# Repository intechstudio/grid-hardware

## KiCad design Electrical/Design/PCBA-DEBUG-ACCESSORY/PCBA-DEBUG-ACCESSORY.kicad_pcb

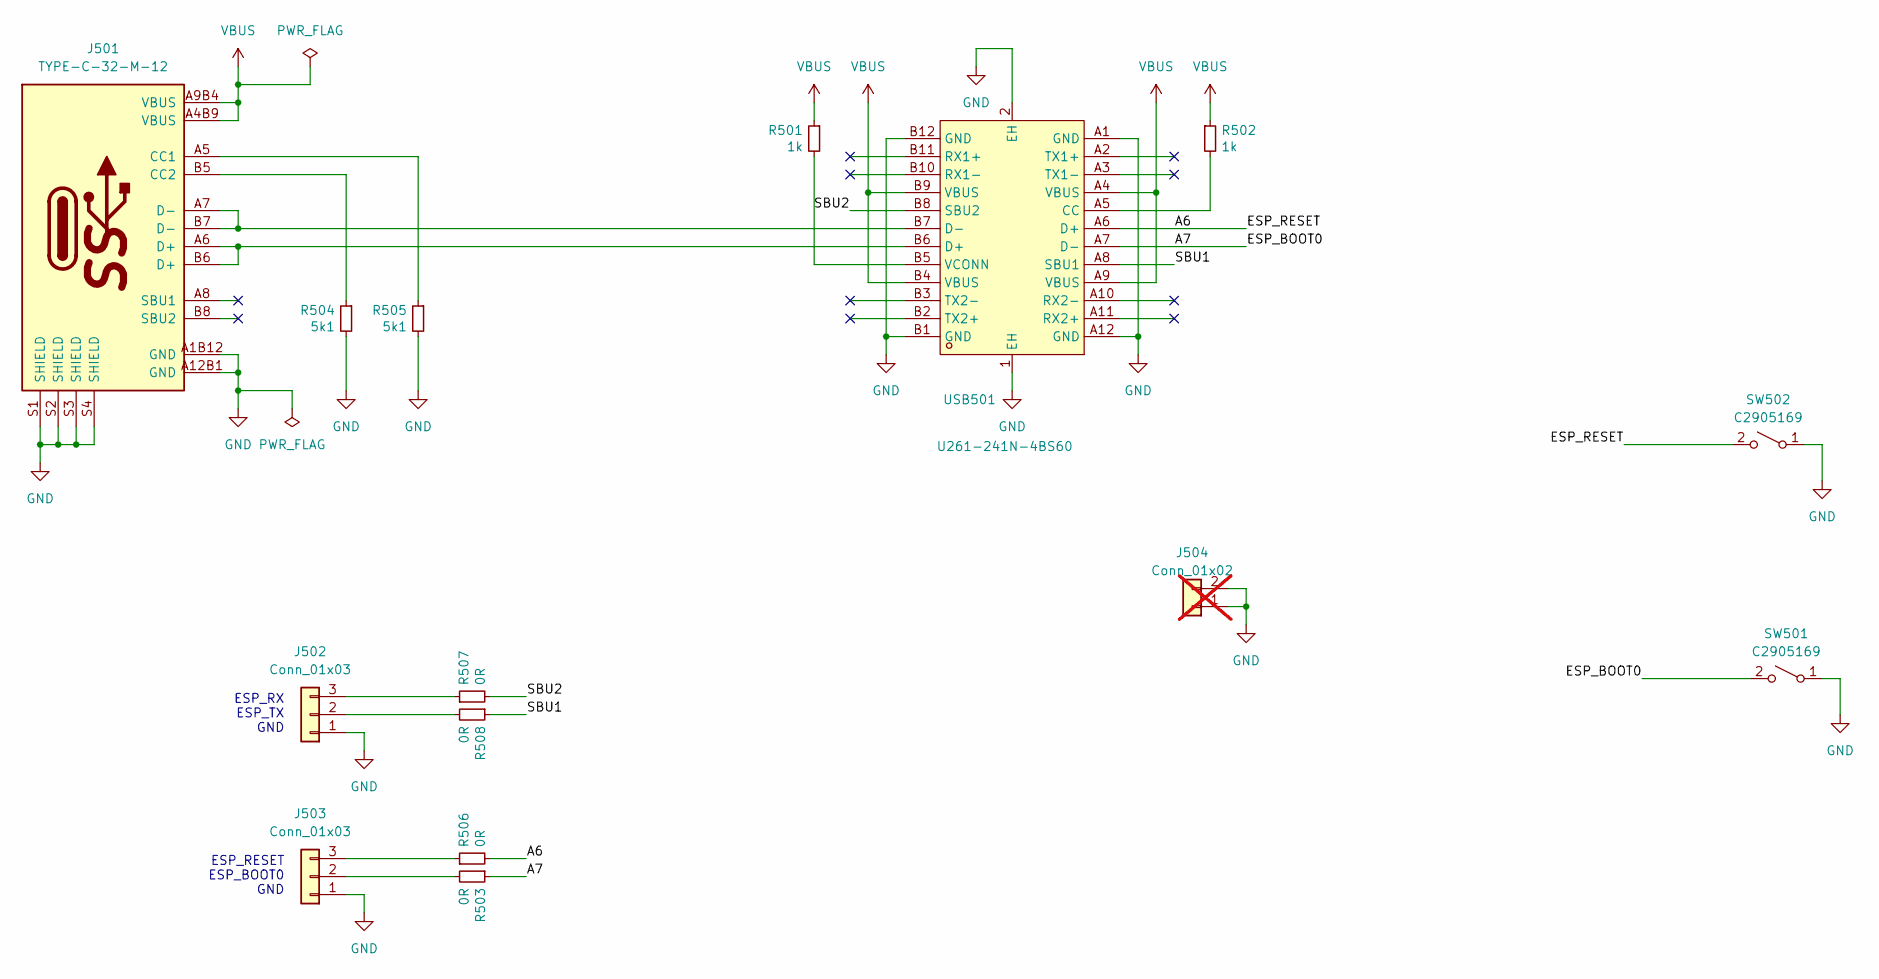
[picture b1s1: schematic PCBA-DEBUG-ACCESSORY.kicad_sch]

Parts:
J501: TYPE-C-32-M-12; USB_C_Korean_Hroparts_TYPE-C-31-M-12
J502, J503: Conn_01x03; PinHeader_1x03_P2.54mm_Vertical
J504: Conn_01x02; OscilloscopeGround; not fitted
R501, R502: 1k; RES_0402
R503, R506, R507, R508: 0R; RES_0402
R504, R505: 5k1; RES_0402
SW501, SW502: C2905169; SW_SPST_CK_RS282G05A3
USB501: U261-241N-4BS60; USB-TYPE-C-SMD_U261-241N-4BS60; LCSC Part C319150

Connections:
/A6: R506.2, SW502.2 (B), USB501.A6 (D+)
/A7: R503.1, SW501.2 (B), USB501.A7 (D-)
/SBU1: R508.1, USB501.A8 (SBU1)
/SBU2: R507.2, USB501.B8 (SBU2)
GND: J501.A1B12 (GND), J501.A12B1 (GND), J501.S1 (SHIELD), J501.S2 (SHIELD), J501.S3 (SHIELD), J501.S4 (SHIELD), J502.1, J503.1, J504.1, J504.2, R504.2, R505.2, SW501.1 (A), SW502.1 (A), USB501.1 (EH), USB501.2 (EH), USB501.A1 (GND), USB501.A12 (GND), USB501.B1 (GND), USB501.B12 (GND)
unnamed: J501.A5 (CC1), R505.1
unnamed: J501.B5 (CC2), R504.1
unnamed: J501.A6 (D+), J501.B6 (D+), USB501.B6 (D+)
unnamed: J501.A7 (D-), J501.B7 (D-), USB501.B7 (D-)
unnamed: J502.2, R508.2
unnamed: J502.3, R507.1
unnamed: J503.2, R503.2
unnamed: J503.3, R506.1
unnamed: R502.2, USB501.A5 (CC)
unnamed: R501.2, USB501.B5 (VCONN)
VBUS: J501.A4B9 (VBUS), J501.A9B4 (VBUS), R501.1, R502.1, USB501.A4 (VBUS), USB501.A9 (VBUS), USB501.B4 (VBUS), USB501.B9 (VBUS)

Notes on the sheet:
ESP_RESET ESP_BOOT0 GND
ESP_RX ESP_TX GND

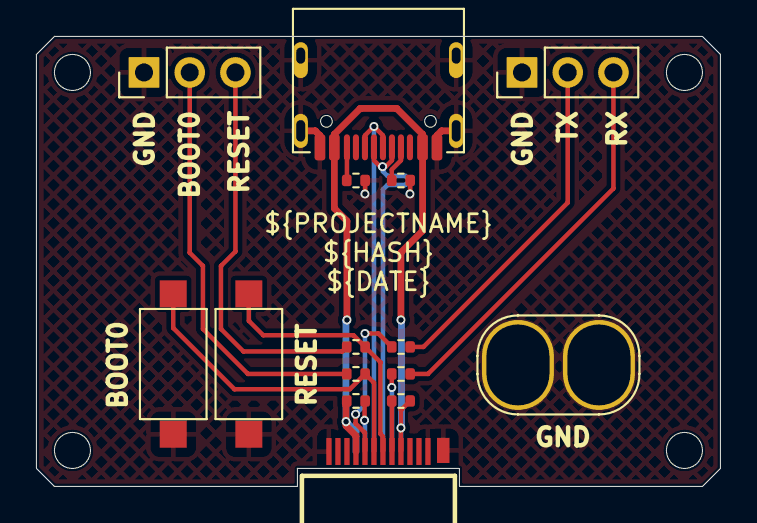
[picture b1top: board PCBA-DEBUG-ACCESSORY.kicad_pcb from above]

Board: 2 copper layers, 38.0 x 25.0 mm, 16 parts (1 on the bottom side), 16 nets.

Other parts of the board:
H534: Outline; OSHWA

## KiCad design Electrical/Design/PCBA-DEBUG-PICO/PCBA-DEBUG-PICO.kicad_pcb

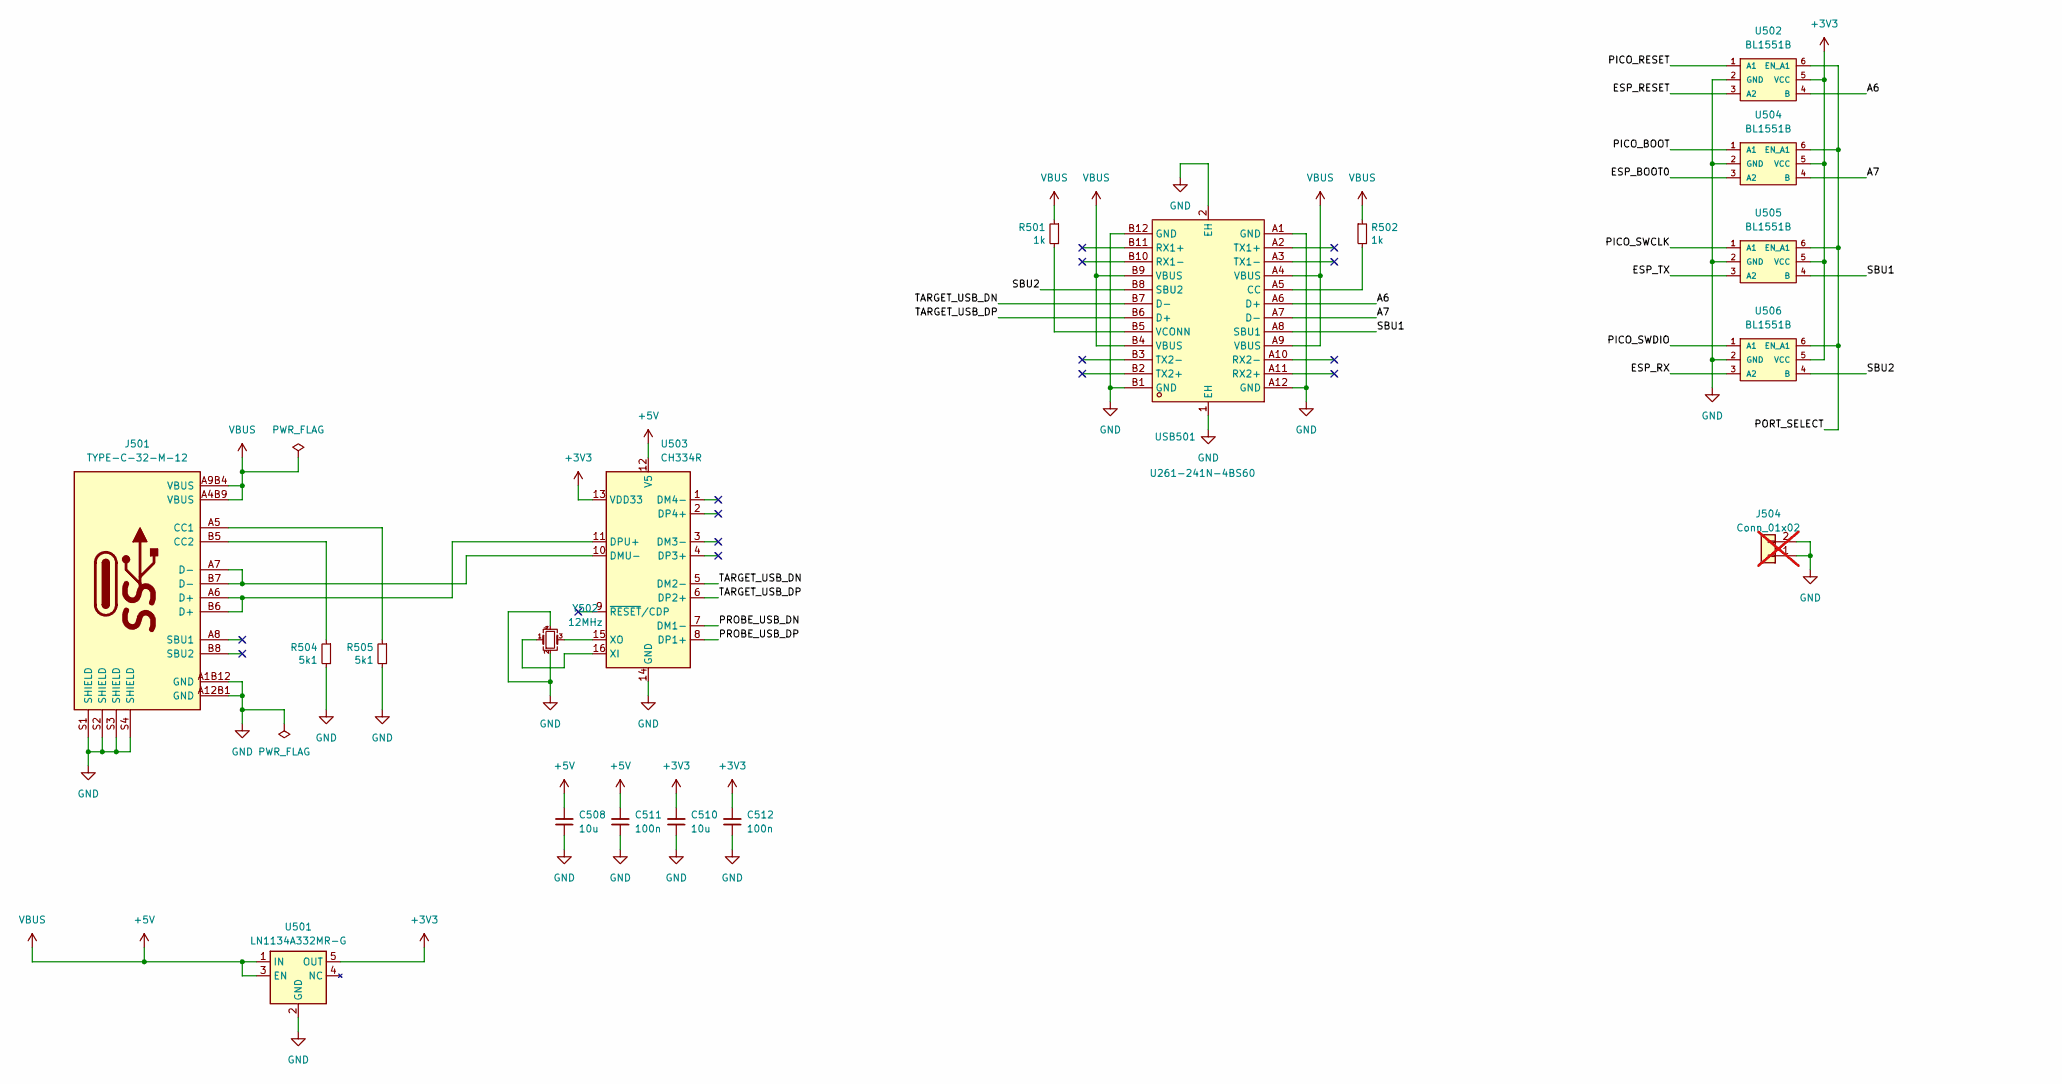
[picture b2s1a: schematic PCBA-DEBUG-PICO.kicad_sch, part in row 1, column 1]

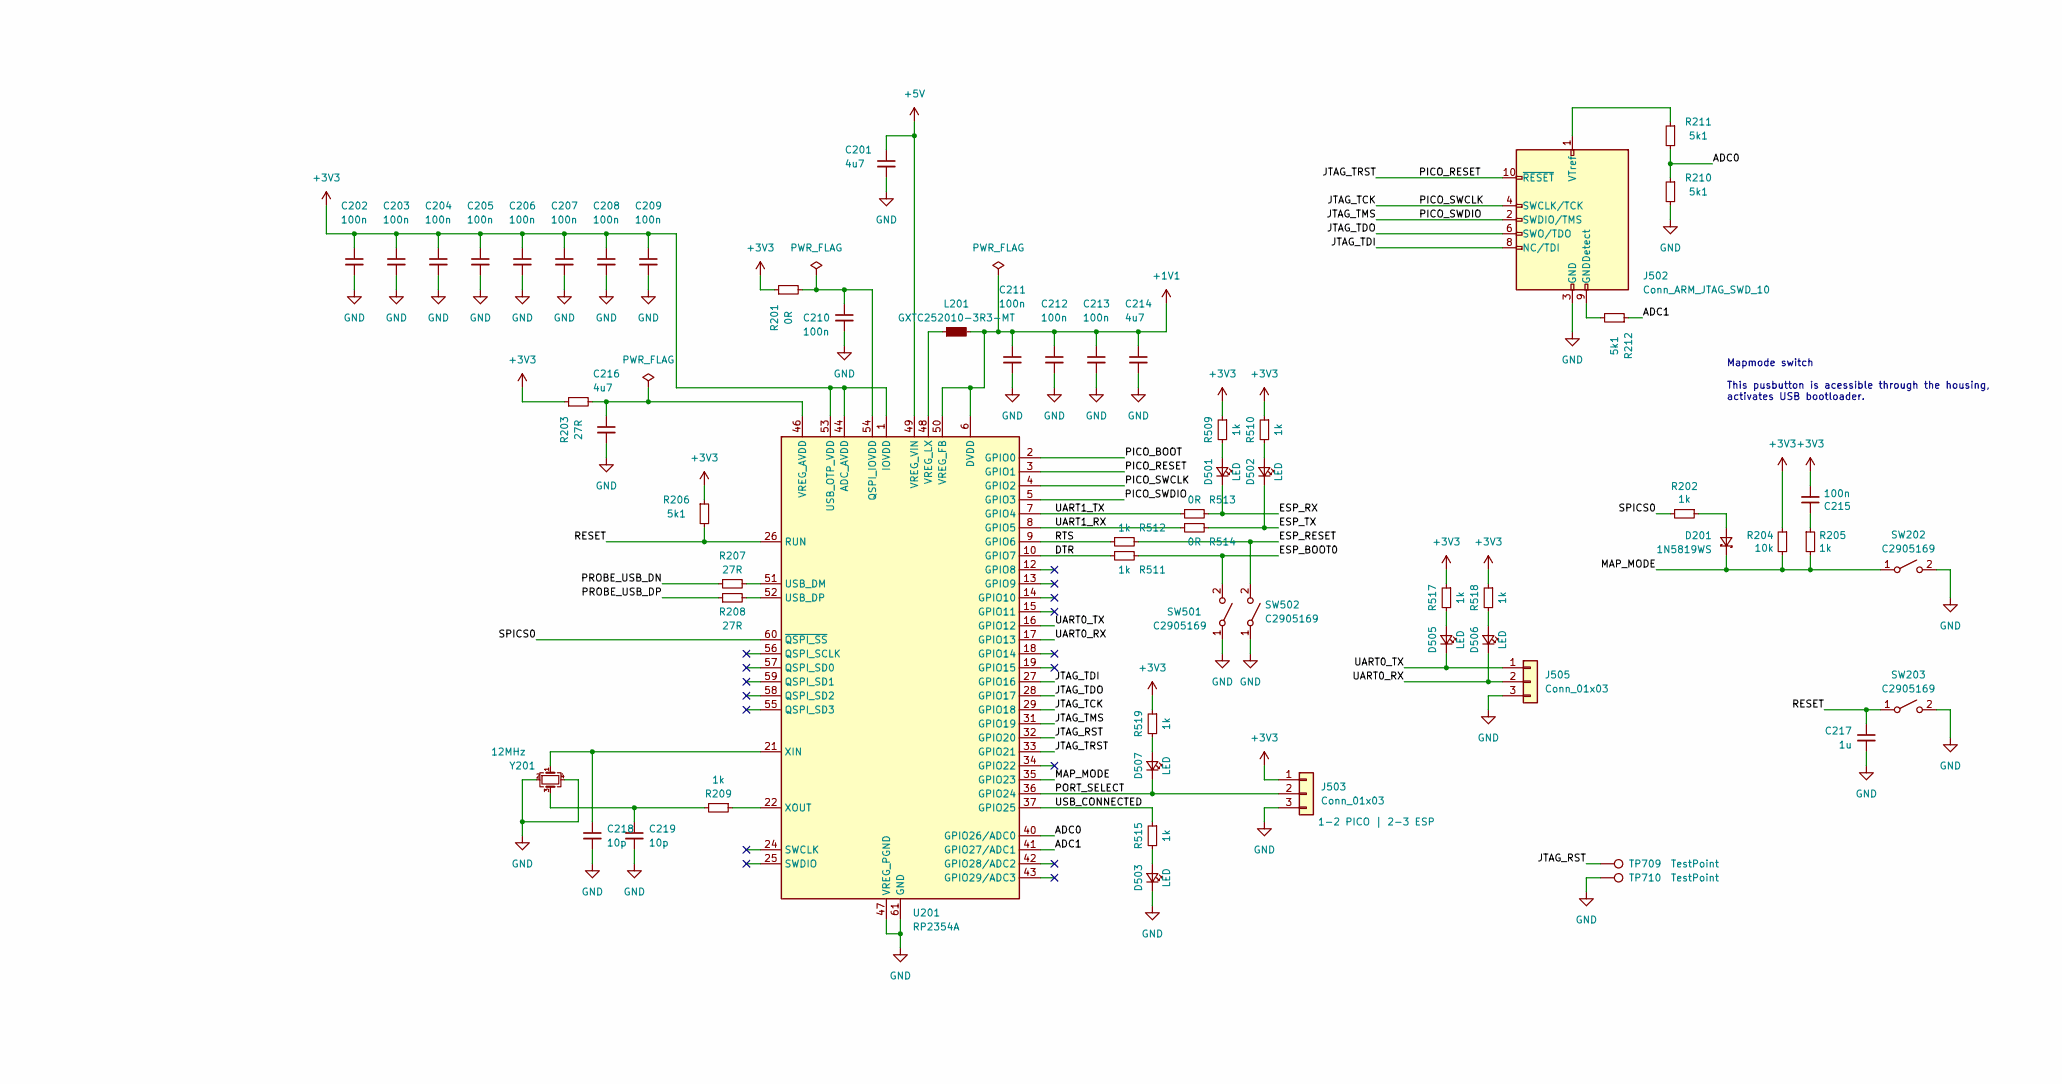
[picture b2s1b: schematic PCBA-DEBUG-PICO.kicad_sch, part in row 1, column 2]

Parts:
C201, C214, C216: 4u7; CAP_0402
C202, C203, C204, C205, C206, C207, C208, C209, C210, C211, C212, C213, C215, C511, C512: 100n; CAP_0402
C217: 1u; CAP_0402
C218, C219: 10p; CAP_0402
C508, C510: 10u; CAP_0402
D201: 1N5819WS; D_SOD-323
D501, D502, D503, D505, D506, D507: LED; LED_0402_1005Metric
J501: TYPE-C-32-M-12; USB_C_Korean_Hroparts_TYPE-C-31-M-12
J502: Conn_ARM_JTAG_SWD_10; IDC-SMD_10P-P1.27-3220-10-0300-00
J503, J505: Conn_01x03; PinHeader_1x03_P2.54mm_Vertical_SMD_Pin1Left
J504: Conn_01x02; OscilloscopeGround; not fitted
L201: GXTC252010-3R3-MT; L_1008_2520Metric
R201, R513, R514: 0R; RES_0402
R202, R205, R209, R501, R502, R509, R510, R511, R512, R515, R517, R518, R519: 1k; RES_0402
R203, R207, R208: 27R; RES_0402
R204: 10k; RES_0402
R206, R210, R211, R212, R504, R505: 5k1; RES_0402
SW202, SW203, SW501, SW502: C2905169; SW_SPST_CK_RS282G05A3
TP709: TestPoint; TestPoint_Pad_D1.0mm
TP710: TestPoint; TestPoint_Pad_1.0x1.0mm
U201: RP2354A; QFN-60-1EP_7x7mm_P0.4mm_EP3.4x3.4mm
U501: LN1134A332MR-G; SOT-23-5
U502, U504, U505, U506: BL1551B; SOT-363_SC-70-6
U503: CH334R; QSOP-16_3.9x4.9mm_P0.635mm
USB501: U261-241N-4BS60; USB-TYPE-C-SMD_U261-241N-4BS60; LCSC Part C319150
Y201, Y502: 12MHz; Crystal_SMD_Abracon_ABM8G-4Pin_3.2x2.5mm

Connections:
+1V1: C211.1, C212.1, C213.1, C214.1, L201.2, U201.6 (DVDD), U201.23 (DVDD), U201.39 (DVDD), U201.50 (VREG_FB)
+3V3: C202.1, C203.1, C204.1, C205.1, C206.1, C207.1, C208.1, C209.1, C215.2, C510.2, C512.2, J503.1, R201.1, R203.1, R204.1, R206.1, R509.1, R510.1, R517.1, R518.1, R519.1, U201.1 (IOVDD), U201.11 (IOVDD), U201.20 (IOVDD), U201.30 (IOVDD), U201.38 (IOVDD), U201.44 (ADC_AVDD), U201.45 (IOVDD), U201.53 (USB_OTP_VDD), U501.5 (OUT), U502.5 (VCC), U503.13 (VDD33), U504.5 (VCC), U505.5 (VCC), U506.5 (VCC)
+5V: C201.1, C508.2, C511.2, J501.A4B9 (VBUS), J501.A9B4 (VBUS), R501.1, R502.1, U201.49 (VREG_VIN), U501.1 (IN), U501.3 (EN), U503.12 (V5), USB501.A4 (VBUS), USB501.A9 (VBUS), USB501.B4 (VBUS), USB501.B9 (VBUS)
/A6: U502.4 (B), USB501.A6 (D+)
/A7: U504.4 (B), USB501.A7 (D-)
/ADC0: R210.1, R211.2, U201.40 (GPIO26/ADC0)
/ADC1: R212.1, U201.41 (GPIO27/ADC1)
/DTR: R511.1, U201.10 (GPIO7)
/ESP_BOOT0: R511.2, SW501.2 (B), U504.3 (A2)
/ESP_RESET: R512.2, SW502.2 (B), U502.3 (A2)
/ESP_RX: D501.1 (K), R513.2, U506.3 (A2)
/ESP_TX: D502.1 (K), R514.2, U505.3 (A2)
/JTAG_RST: TP709.1 (1_1), U201.32 (GPIO20)
/JTAG_TCK: J502.4 (SWCLK/TCK), U201.4 (GPIO2), U201.29 (GPIO18), U505.1 (A1)
/JTAG_TDI: J502.8 (NC/TDI), U201.27 (GPIO16)
/JTAG_TDO: J502.6 (SWO/TDO), U201.28 (GPIO17)
/JTAG_TMS: J502.2 (SWDIO/TMS), U201.5 (GPIO3), U201.31 (GPIO19), U506.1 (A1)
/JTAG_TRST: J502.10 (~RESET), U201.3 (GPIO1), U201.33 (GPIO21), U502.1 (A1)
/MAP_MODE: D201.1 (K), R204.2, R205.2, SW202.1 (A), U201.35 (GPIO23)
/PICO_BOOT: U201.2 (GPIO0), U504.1 (A1)
/PORT_SELECT: D507.1 (K), J503.2, U201.36 (GPIO24), U502.6 (EN_A1), U504.6 (EN_A1), U505.6 (EN_A1), U506.6 (EN_A1)
/PROBE_USB_DN: R207.1, U503.7 (DM1-)
/PROBE_USB_DP: R208.1, U503.8 (DP1+)
/RESET: C217.1, R206.2, SW203.1 (A), U201.26 (RUN)
/RTS: R512.1, U201.9 (GPIO6)
/SBU1: U505.4 (B), USB501.A8 (SBU1)
/SBU2: U506.4 (B), USB501.B8 (SBU2)
/SPICS0: R202.2, U201.60 (~QSPI_SS)
/TARGET_USB_DN: U503.5 (DM2-), USB501.B7 (D-)
/TARGET_USB_DP: U503.6 (DP2+), USB501.B6 (D+)
/UART0_RX: D506.1 (K), J505.2, U201.17 (GPIO13)
/UART0_TX: D505.1 (K), J505.1, U201.16 (GPIO12)
/UART1_RX: R514.1, U201.8 (GPIO5)
/UART1_TX: R513.1, U201.7 (GPIO4)
/USB_CONNECTED: R515.1, U201.37 (GPIO25)
GND: C201.2, C202.2, C203.2, C204.2, C205.2, C206.2, C207.2, C208.2, C209.2, C210.2, C211.2, C212.2, C213.2, C214.2, C216.2, C217.2, C218.2, C219.2, C508.1, C510.1, C511.1, C512.1, D503.1 (K), J501.A1B12 (GND), J501.A12B1 (GND), J501.S1 (SHIELD), J501.S2 (SHIELD), J501.S3 (SHIELD), J501.S4 (SHIELD), J502.3 (GND), J502.5 (GND), J503.3, J504.1, J504.2, J505.3, R210.2, R504.2, R505.2, SW202.2 (B), SW203.2 (B), SW501.1 (A), SW502.1 (A), TP710.1 (1_1), U201.47 (VREG_PGND), U201.61 (GND), U501.2 (GND), U502.2 (GND), U503.14 (GND), U504.2 (GND), U505.2 (GND), U506.2 (GND), USB501.1 (EH), USB501.2 (EH), USB501.A1 (GND), USB501.A12 (GND), USB501.B1 (GND), USB501.B12 (GND), Y201.2, Y201.4, Y502.2, Y502.4
unnamed: C215.1, R205.1
unnamed: C219.1, R209.2, Y201.3
unnamed: D201.2 (A), R202.1
unnamed: D501.2 (A), R509.2
unnamed: D502.2 (A), R510.2
unnamed: D503.2 (A), R515.2
unnamed: D505.2 (A), R517.2
unnamed: D506.2 (A), R518.2
unnamed: D507.2 (A), R519.2
unnamed: J501.A5 (CC1), R505.1
unnamed: J501.B5 (CC2), R504.1
unnamed: J502.9 (GNDDetect), R212.2
unnamed: J502.1 (VTref), R211.1
unnamed: C210.1, R201.2, U201.54 (QSPI_IOVDD)
unnamed: R207.2, U201.51 (USB_DM)
unnamed: R208.2, U201.52 (USB_DP)
unnamed: C216.1, R203.2, U201.46 (VREG_AVDD)
unnamed: L201.1, U201.48 (VREG_LX)
unnamed: C218.1, U201.21 (XIN), Y201.1
unnamed: R209.1, U201.22 (XOUT)
unnamed: J501.A7 (D-), J501.B7 (D-), U503.10 (DMU-)
unnamed: J501.A6 (D+), J501.B6 (D+), U503.11 (DPU+)
unnamed: U503.16 (XI), Y502.1
unnamed: U503.15 (XO), Y502.3
unnamed: R502.2, USB501.A5 (CC)
unnamed: R501.2, USB501.B5 (VCONN)

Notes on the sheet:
Mapmode switch This pusbutton is acessible through the housing, activates USB bootloader.

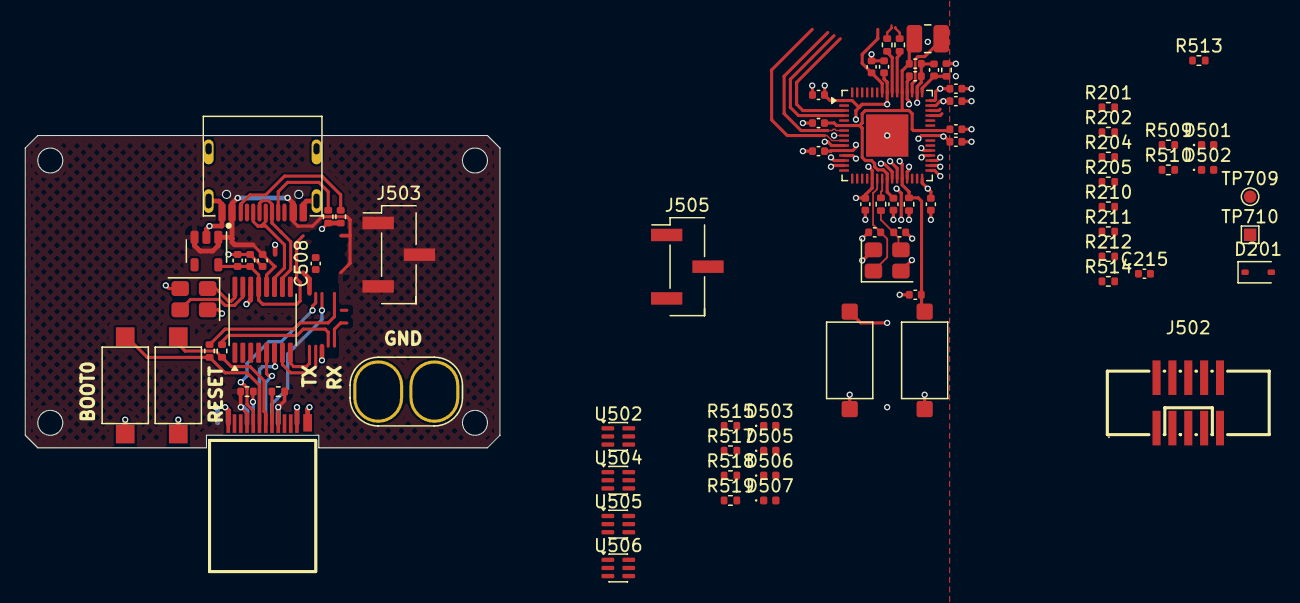
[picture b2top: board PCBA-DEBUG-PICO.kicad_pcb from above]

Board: 4 copper layers, 38.0 x 25.0 mm, 79 parts (1 on the bottom side), 62 nets.

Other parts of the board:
H534: Outline; OSHWA
